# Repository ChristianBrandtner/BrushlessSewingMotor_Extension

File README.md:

# BrushlessSewingMotor_Extension
&nbsp;&nbsp;&nbsp;&nbsp;&nbsp;&nbsp;&nbsp;&nbsp;&nbsp;&nbsp;

contact: github1@brandtner.net

## 11/2022  ! Project is in progress, ask before you order PCB or other things. !

## INTRODUCTION

This is a extension for a cheap chinese 550/750W brushless servo motor for external control of speed, direction, etc.
to use in in e.g. Mini Lathe

first test with switch and potentiometer:
https://www.youtube.com/watch?v=qao7Rex1lZU

## STATUS
7.11.2024

Ein neues ISO Interface ist in Arbeit aber noch nicht fertiggestellt. 
Die Software ermöglicht es jetzt die komplette Steuerung des Motorkontollers zu übernehmen, inklusive der Einstellungen für die Motorparameter im Kontroller. Das bedeutet daß das Bedienpanel des BLDC-Motors nicht mehr in Griffweite sein muss.

Im Moment pausiert die Entwicklung weil zuwenig Bedarf dafür zu erkennen ist.

A new ISO interface is in the works but not yet finished. The software now makes it possible to take over complete control of the motor controller, including the settings for the motor parameters in the controller. This means that the control panel of the BLDC motor no longer has to be within reach.

Development is currently on hold because there is not enough demand for it.

14.2.2023

RPM Sensor

05.09.2022

Beim Einbau in das Steuergehäuse habe ich nun festgestellt das es Änderungsbedarf gibt, es ist ziemlich eng und die Anordnung der Anschlüsse passt nicht so wirklich gut.

Deshalb wird es eine zweigeteilte Lösung geben, 1. das Iso Ínterface, montiert auf dem SMC Controller, 2. davon getrennt die Steuerungsplatine, dann neu mit einem Ardunino Nano wegen der USB-Schnittstelle für einfache Updates.
Durch die Trennung ergibt sich auch die Mögichkeit eine andere Steuerung zu verwenden, z.B. Blackpill STM32F411. Der Ardunio ist schon arg an der Grenze des Flashspeichers.

Next Version (11/2022):

08.07.2022

Die ursprüngĺiche Planung auf eine Hardwaredrehzahlmessung zu verzichten werde ich nicht mehr weiterverfolgen.
Die Softwarelösung funktioniert zwar zufriedenstellend, auch unter berücksichtigung des Getriebeschalters und der Untersetzungen von Motor und Getriebe, aber der Atmega ist durch die vielen Einstellungsmenüs am Ende der Kapazität.
Deshalb ist ein Drehzahlsensor an der Spindel erforderlich, damit entfällt die ganze Software für die Drehzahlberechnung und es ist Platz um die Schnittgeschwindigkeit für den Werkstückdurchmesser anzuzeigen.
Das finde ich nützlicher als den Drehzahlsensor einzusparen.
An der Hardware der Platine ändert sich nichts, war alles schon vorgesehen.

07.07.2022

Version 14.5

Änderungen an der Platine
Grund:
Einfügen eines optionalen ISP-Steckers.
Anschluss der RPM Sensors nach PB0 (ICP1) verlegt.
optinonal weitere Anschlussbuchse für den Pedalanschluss vorgesehen, zum direkten Kabelanschluss des Pedalkabels
an den originalen Stecker des SMC. Kein zusätzlicher JST Stecker J9 auf dem SMC Board notwendig. 

22.6.2022

Version 14.2

Änderungen an der Platine
Grund:
JST Stecker J3 Fehler in der Ausrichtung beseitigt

20.6.2022

Version 14.1

Änderungen an der Platine
Grund:
OK2 Anschlüsse vertauscht, optionale Widerstände R6,R30,R31
JST Stecker J3, Ausrichtung getauscht damit fertig konfektionierte Kabel zum SMC verwendet werden können.
Schaltung getestet (ohne RPM-Sensor und analog 0-10V Eingang, alles optional)

Wesentliche Funktionen der Software funktionieren:
Drehzahlregelung, Richtungsumschaltung, Drehzahlanzeige

03.06.2022 New PCB Version 12.2, Errors in PCB layout fixed. Basic software in progress.

12.05.2022 PCB Version 11.5 with galvanic isolation is in production 

30.04.2022 The goal is to fit the SMC controller board and everything else into the existing lathe front casing.

29.04.2022 optoisolation with separate powersupply is in work.

28.04.2022 under construction and brainstorming.

## PREVIEW

## TODO

TODO: finalize software

## Features

- no changes on Controlerboard or Panelboard needed; 
- can be installed in the housing on existing attachments; 
- speedcontrol, rotary encoder;
- start/stop control,  button with LED; 
- rotation direction control, button with LED;
- securityswitch input for chuck guard;
- spindel RPM display (calculated and maesured)
- original SMC displaypanel can be used at same time 
- high temperture warning;
- rampup and down at start/stop
- isolated inputs/outputs for galvanic isolation from the mains voltage

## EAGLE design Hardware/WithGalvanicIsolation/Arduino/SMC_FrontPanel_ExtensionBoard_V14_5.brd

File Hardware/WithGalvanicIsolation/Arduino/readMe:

this version will no longer be pursued.
14.2.2023

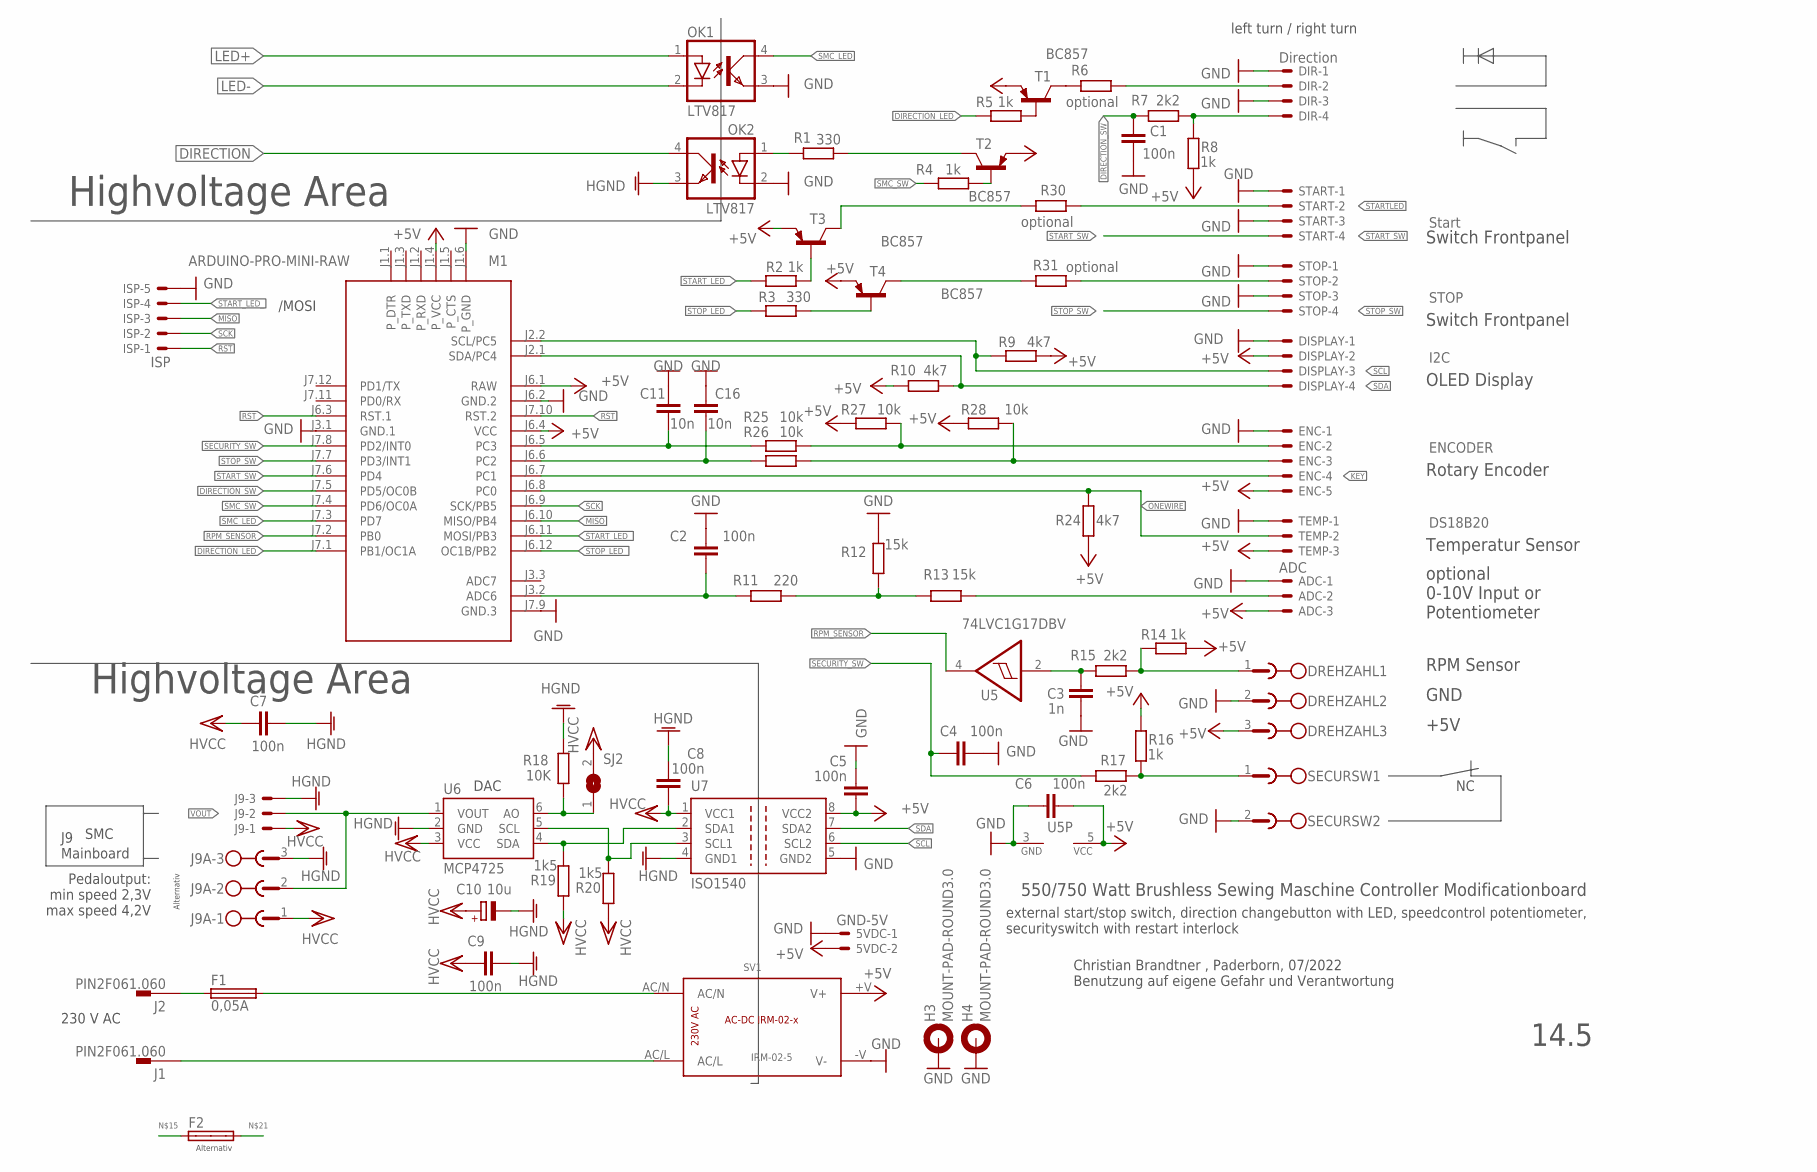
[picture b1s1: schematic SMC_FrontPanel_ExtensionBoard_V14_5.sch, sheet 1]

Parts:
5VDC: GND-5V; JST-XH-02-PACKAGE-ROUND-PAD
ADC: ADC; JST-XH-03-PACKAGE-ROUND-PAD
C1, C2, C4, C5, C6, C7, C8, C9: 100n; C0805
C3: 1n; C0805
C10: 10u; 153CLV-0405
C11, C16: 10n; C0805
DIR: Direction; JST-XH-04-PACKAGE-ROUND-PAD
DISPLAY: I2C; JST-XH-04-PACKAGE-ROUND-PAD
DREHZAHL: MCV_1.5/3/-G-3.5; 1843619
ENC: ENCODER; JST-XH-05-PACKAGE-ROUND-PAD
F1: 0,05A; MTA501100
F2: SHK20L
H3, H4: MOUNT-PAD-ROUND3.0; 3,0-PAD
ISP: ISP; JST-XH-05-PACKAGE-ROUND-PAD
J1, J2: PIN2F061.060; F061.060
J9: JST-XH-03-PIN-ROUND-PAD; JST-XH-03-PACKAGE-ROUND-PAD
J9A-: MCV_1.5/3/-G-3.5; 1843619
M1: ARDUINO-PRO-MINI-RAW; ARDUINO-PRO-MINI
OK1, OK2: LTV817; SMD4-7
R1, R3: 330; R0805
R2, R4, R5, R8, R14, R16: 1k; R0805
R6, R30, R31: optional; R0805
R7, R15, R17: 2k2; R0805
R9, R10, R24: 4k7; R0805
R11: 220; R0805
R12, R13: 15k; R0805
R18: 10K; R0805
R19, R20: 1k5; R0805
R25, R26, R27, R28: 10k; R0805
SECURSW: MCV_1,5/2-G-3,5; 1843606
SJ2: SJ
START: Start; JST-XH-04-PACKAGE-ROUND-PAD
STOP: STOP; JST-XH-04-PACKAGE-ROUND-PAD
SV1: IRM-02-5; IRM-02-X
T1, T2, T3, T4: BC857; SOT23-BEC
TEMP: DS18B20; JST-XH-03-PACKAGE-ROUND-PAD
U5: 74LVC1G17DBV; SOT23-5
U6: MCP4725; SOT23-6
U7: ISO1540; SO-08

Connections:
+5V: 5VDC.2, ADC.3, C5.1, C6.1, DISPLAY.2, DREHZAHL.3, ENC.5, M1.J1.4 (P_VCC), M1.J6.1 (RAW), M1.J6.4 (VCC), R8.2, R9.1, R10.1, R14.1, R16.1, R24.2, R27.1, R28.1, SV1.+V (V+), T1.E, T2.E, T3.E, T4.E, TEMP.3, U5.5 (VCC), U7.8 (VCC2)
ADC_POTI: C2.1, M1.J3.2 (ADC6), R11.1
DIRECTION: OK2.4 (COL); also elsewhere on the board
DIRECTION_LED: M1.J7.1 (PB1/OC1A), R5.2
DIRECTION_SW: C1.2, M1.J7.5 (PD5/OC0B), R7.1
GND: 5VDC.1, ADC.1, C1.1, C2.2, C3.1, C4.2, C5.2, C6.2, C11.2, C16.2, DIR.1, DIR.3, DISPLAY.1, DREHZAHL.2, ENC.1, H3.B3,0, H4.B3,0, ISP.5, M1.J1.6 (P_GND), M1.J3.1 (GND.1), M1.J6.2 (GND.2), M1.J7.9 (GND.3), OK1.3 (EMIT), OK2.2 (C), R12.2, SECURSW.2, START.1, START.3, STOP.1, STOP.3, SV1.-V (V-), TEMP.1, U5.3 (GND), U7.5 (GND2)
HGND: C7.1, C8.2, C9.1, C10.-, J9.3, J9A-.3, OK2.3 (EMIT), R18.1, U6.2 (GND), U7.4 (GND1); also elsewhere on the board
HVCC: C7.2, C8.1, C9.2, C10.+, J9.1, J9A-.1, R19.2, R20.2, SJ2.2, U6.3 (VCC), U7.1 (VCC1); also elsewhere on the board
KEY: ENC.4, M1.J6.7 (PC1)
LED+: OK1.1 (A); also elsewhere on the board
LED-: OK1.2 (C); also elsewhere on the board
MISO: ISP.3, M1.J6.10 (MISO/PB4)
unnamed: OK2.1 (A), R1.2
unnamed: R1.1, T2.C
unnamed: R30.1, START.2
unnamed: R2.1, T3.B
unnamed: C3.2, R15.1, U5.2 (I)
unnamed: R3.1, T4.B
unnamed: R18.2, SJ2.1, U6.6 (AO)
unnamed: F1.1, F2.1A, J2.A1, J2.A2
unnamed: DREHZAHL.1, R14.2, R15.2
unnamed: R16.2, R17.2, SECURSW.1
unnamed: R31.2, T4.C
unnamed: R11.2, R12.1, R13.2
unnamed: ADC.2, R13.1
unnamed: F1.2, F2.2A, SV1.AC/N
unnamed: J1.A1, J1.A2, SV1.AC/L
unnamed: R6.2, T1.C
unnamed: DIR.2, R6.1
unnamed: R5.1, T1.B
unnamed: R4.1, T2.B
unnamed: R20.1, U6.5 (SCL), U7.3 (SCL1)
unnamed: DIR.4, R7.2, R8.1
unnamed: C16.1, M1.J6.6 (PC2), R26.1
unnamed: C11.1, M1.J6.5 (PC3), R25.1
unnamed: ENC.2, R25.2, R27.2
unnamed: ENC.3, R26.2, R28.2
unnamed: R31.1, STOP.2
ONEWIRE: M1.J6.8 (PC0), R24.1, TEMP.2
RPM_SENSOR: M1.J7.2 (PB0), U5.4 (O)
RST: ISP.1, M1.J6.3 (RST.1), M1.J7.10 (RST.2)
SCK: ISP.2, M1.J6.9 (SCK/PB5)
SCL: DISPLAY.3, M1.J2.2 (SCL/PC5), R9.2, U7.6 (SCL2)
SDA: DISPLAY.4, M1.J2.1 (SDA/PC4), R10.2, U7.7 (SDA2)
SDA_HV: R19.1, U6.4 (SDA), U7.2 (SDA1)
SECURITY_SW: C4.1, M1.J7.8 (PD2/INT0), R17.1
SMC_LED: M1.J7.3 (PD7), OK1.4 (COL)
SMC_SW: M1.J7.4 (PD6/OC0A), R4.2
STARTLED: R30.2, T3.C
START_LED_: ISP.4, M1.J6.11 (MOSI/PB3), R2.2
START_SW: M1.J7.6 (PD4), START.4
STOP_LED_: M1.J6.12 (OC1B/PB2), R3.2
STOP_SW: M1.J7.7 (PD3/INT1), STOP.4
VOUT: J9.2, J9A-.2, U6.1 (VOUT)

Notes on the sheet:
left turn / right turn
SMC
Pedaloutput: min speed 2,3V max speed 4,2V
DAC
Highvoltage Area
14.5
OLED Display
Rotary Encoder
Temperatur Sensor
Switch Frontpanel
optional 0-10V Input or Potentiometer
RPM Sensor
550/750 Watt Brushless Sewing Maschine Controller Modificationboard
external start/stop switch, direction changebutton with LED, speedcontrol potentiometer, securityswitch with restart interlock
Christian Brandtner , Paderborn, 07/2022 Benutzung auf eigene Gefahr und Verantwortung
230 V AC
J9 Mainboard
+5V
GND
Alternativ
/MOSI

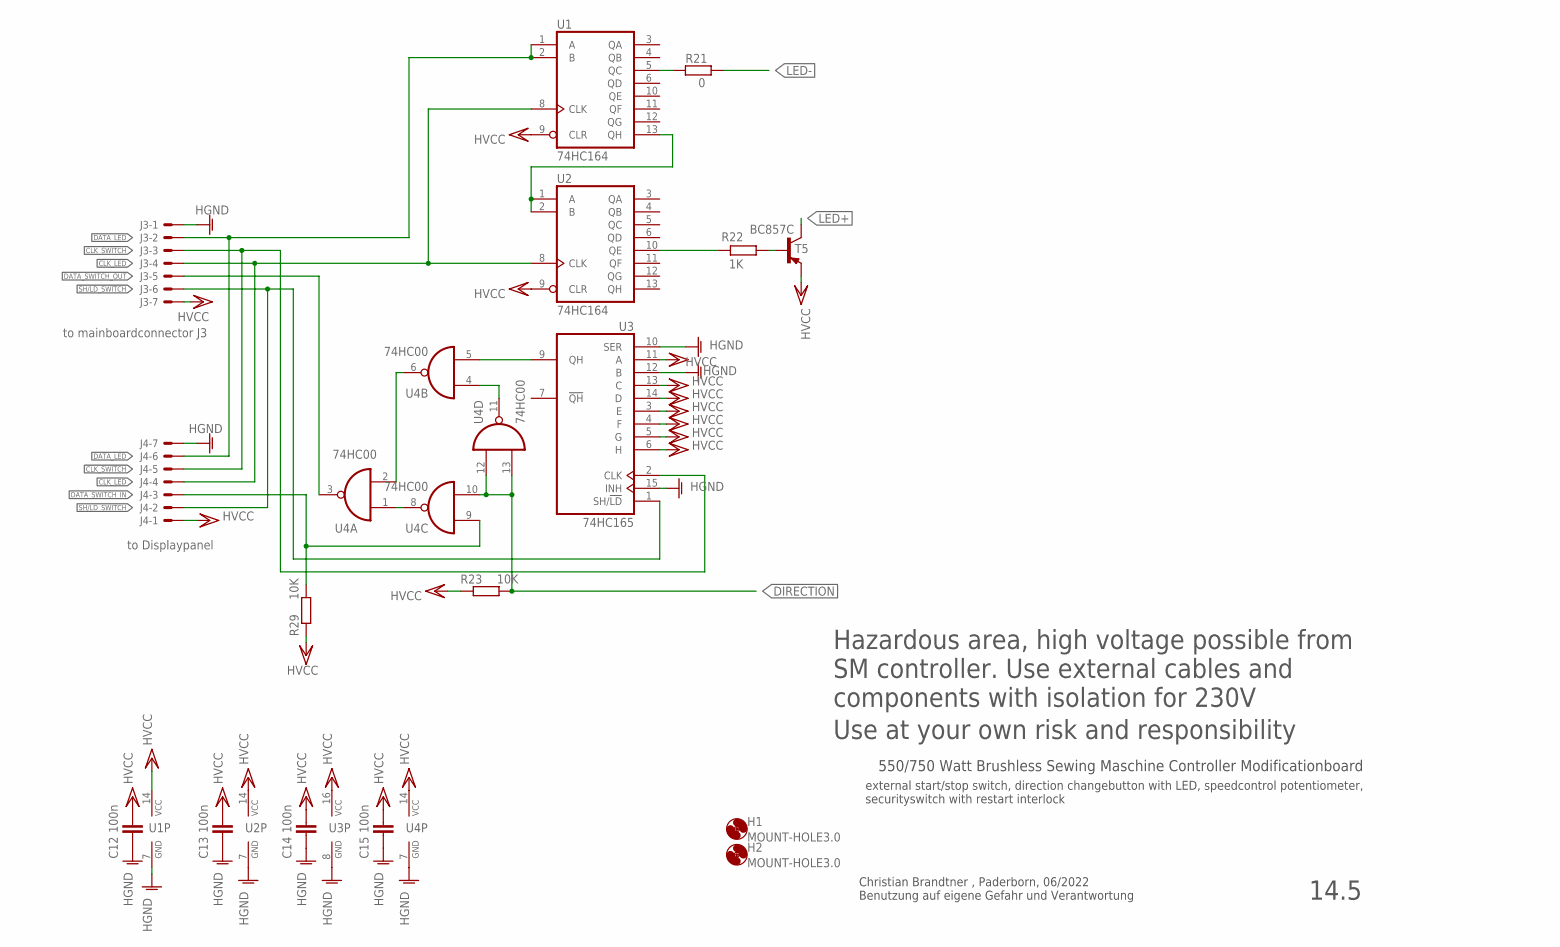
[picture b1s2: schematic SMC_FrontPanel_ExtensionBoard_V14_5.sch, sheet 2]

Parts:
C12, C13, C14, C15: 100n; C0805
H1, H2: MOUNT-HOLE3.0; 3,0
J3: to mainboardconnector J3; JST-XH-07-PACKAGE-ROUND-PAD
J4: to Displaypanel; JST-XH-07-PACKAGE-ROUND-PAD
R21: 0; R0805
R22: 1K; R0805
R23, R29: 10K; R0805
T5: BC857C; SOT23-BEC
U1, U2: 74HC164; SO14
U3: 74HC165; SO16
U4: 74HC00; SO14

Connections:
CLK_LED: J3.4, J4.4, U1.8 (CLK), U2.8 (CLK)
CLK_SWITCH: J3.3, J4.5, U3.2 (CLK)
DATA_LED: J3.2, J4.6, U1.1 (A), U1.2 (B)
DATA_SWITCH_IN: J4.3, R29.1, U4.9 (I0)
DATA_SWITCH_OUT: J3.5, U4.3 (O)
DIRECTION: R23.1, U4.10 (I1), U4.12 (I0), U4.13 (I1); also elsewhere on the board
G: U1.13 (QH), U2.1 (A), U2.2 (B)
HGND: C12.1, C13.1, C14.1, C15.1, J3.1, J4.7, U1.7 (GND), U2.7 (GND), U3.8 (GND), U3.10 (SER), U3.12 (B), U3.15 (INH), U4.7 (GND); also elsewhere on the board
HVCC: C12.2, C13.2, C14.2, C15.2, J3.7, J4.1, R23.2, R29.2, T5.E, U1.9 (CLR), U1.14 (VCC), U2.9 (CLR), U2.14 (VCC), U3.3 (E), U3.4 (F), U3.5 (G), U3.6 (H), U3.11 (A), U3.13 (C), U3.14 (D), U3.16 (VCC), U4.14 (VCC); also elsewhere on the board
LED+: T5.C; also elsewhere on the board
LED-: R21.2; also elsewhere on the board
unnamed: R22.1, T5.B
unnamed: R21.1, U1.5 (QC)
unnamed: U3.9 (QH), U4.5 (I1)
unnamed: U4.2 (I1), U4.6 (O)
unnamed: U4.1 (I0), U4.8 (O)
unnamed: U4.4 (I0), U4.11 (O)
unnamed: R22.2, U2.10 (QE)
SH/LD_SWITCH: J3.6, J4.2, U3.1 (SH/!LD)

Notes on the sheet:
550/750 Watt Brushless Sewing Maschine Controller Modificationboard
external start/stop switch, direction changebutton with LED, speedcontrol potentiometer, securityswitch with restart interlock
Hazardous area, high voltage possible from SM controller. Use external cables and components with isolation for 230V
Christian Brandtner , Paderborn, 06/2022 Benutzung auf eigene Gefahr und Verantwortung
14.5
Use at your own risk and responsibility

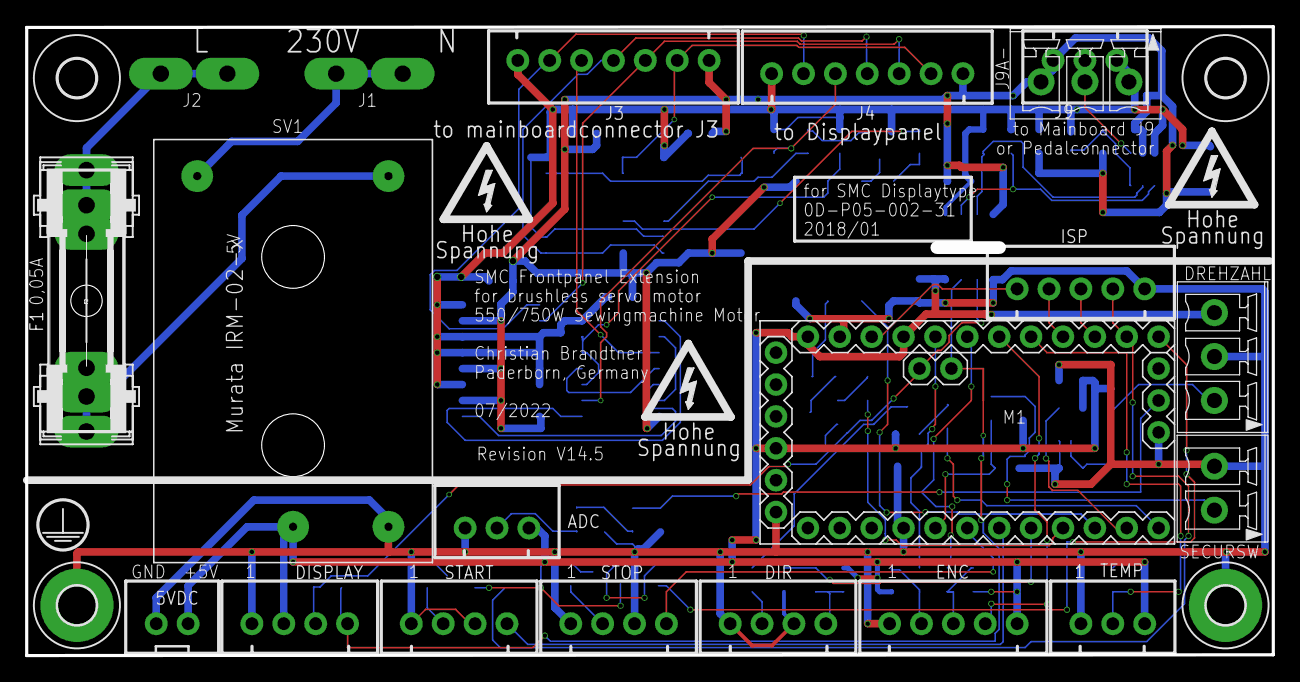
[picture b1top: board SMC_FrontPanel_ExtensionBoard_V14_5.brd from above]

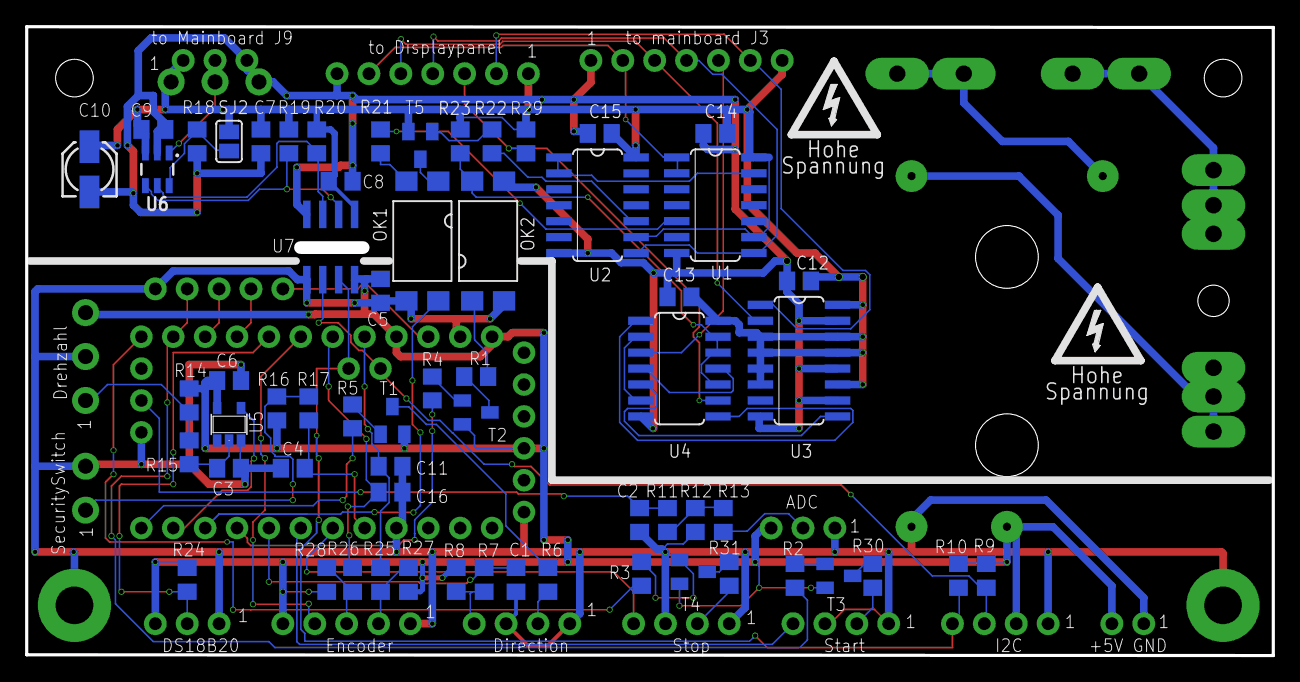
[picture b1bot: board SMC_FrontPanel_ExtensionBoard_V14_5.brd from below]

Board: 2 copper layers, 98.5 x 49.3 mm, 93 parts (62 on the bottom side), 68 nets.

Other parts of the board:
U$53, U$54, U$57: HIGHVOLT1_TOP
U$55, U$56: HIGHVOLT1_BOT
U$58: SCHUTZLEITER

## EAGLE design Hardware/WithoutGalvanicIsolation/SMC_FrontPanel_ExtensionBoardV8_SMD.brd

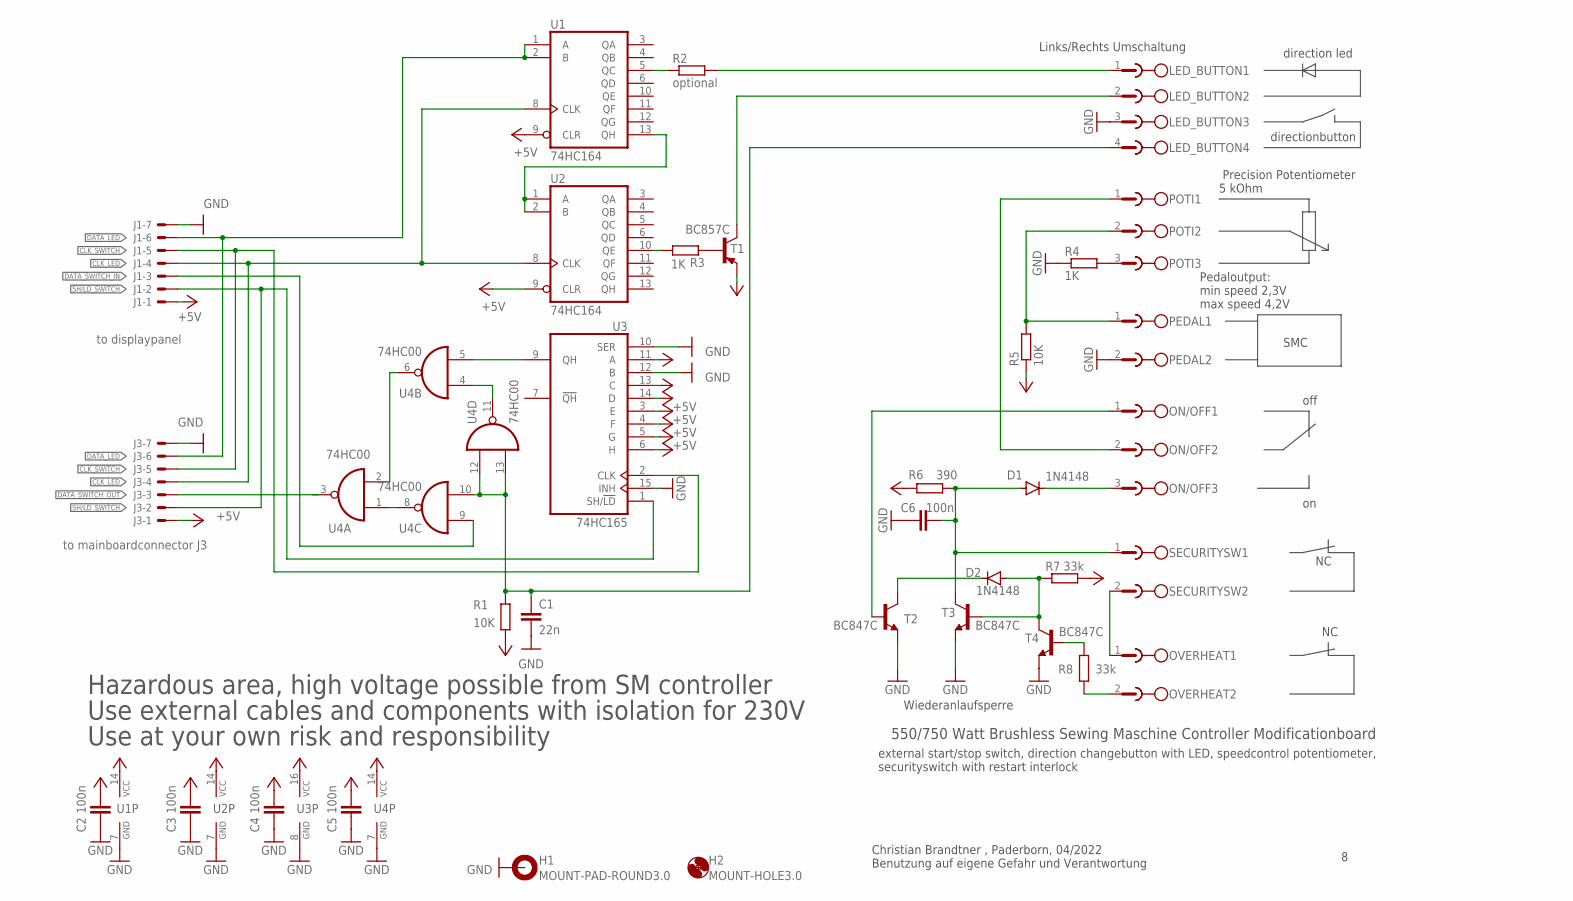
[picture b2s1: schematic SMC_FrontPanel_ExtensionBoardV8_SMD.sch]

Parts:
C1: 22n; C0805
C2, C3, C4, C5, C6: 100n; C0805
D1, D2: 1N4148; SOD323-W
H1: MOUNT-PAD-ROUND3.0; 3,0-PAD
H2: MOUNT-HOLE3.0; 3,0
J1: to displaypanel; JST-XH-07-PACKAGE-ROUND-PAD
J3: to mainboardconnector J3; JST-XH-07-PACKAGE-ROUND-PAD
LED_BUTTON: MC_1.5/4_G_3.5; MC_1.5/4-G-3.5
ON/OFF: MC_1.5/3-G-3.5
OVERHEAT: MC_1.5/2-G-3.5
PEDAL: MC_1.5/2-G-3.5
POTI: MC_1.5/3-G-3.5
R1, R5: 10K; R0805
R2: optional; R0805
R3, R4: 1K; R0805
R6: 390; R0805
R7, R8: 33k; R0805
SECURITYSW: MC_1.5/2-G-3.5
T1: BC857C; SOT23-BEC
T2, T3, T4: BC847C; SOT23-BEC
U1, U2: 74HC164; SO14
U3: 74HC165; SO16
U4: 74HC00; SO14

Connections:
+5V: C2.2, C3.2, C4.2, C5.2, J1.1, J3.1, R1.2, R5.1, R6.2, R7.1, T1.E, U1.9 (CLR), U1.14 (VCC), U2.9 (CLR), U2.14 (VCC), U3.3 (E), U3.4 (F), U3.5 (G), U3.6 (H), U3.11 (A), U3.13 (C), U3.14 (D), U3.16 (VCC), U4.14 (VCC)
CLK_LED: J1.4, J3.4, U1.8 (CLK), U2.8 (CLK)
CLK_SWITCH: J1.5, J3.5, U3.2 (CLK)
DATA_LED: J1.6, J3.6, U1.1 (A), U1.2 (B)
DATA_SWITCH_IN: J1.3, U4.9 (I0)
DATA_SWITCH_OUT: J3.3, U4.3 (O)
G: U1.13 (QH), U2.1 (A), U2.2 (B)
GND: C1.2, C2.1, C3.1, C4.1, C5.1, C6.1, H1.B3,0, J1.7, J3.7, LED_BUTTON.3, PEDAL.2, R4.1, T2.E, T3.E, T4.E, U1.7 (GND), U2.7 (GND), U3.8 (GND), U3.10 (SER), U3.12 (B), U3.15 (INH), U4.7 (GND)
unnamed: R3.1, T1.B
unnamed: LED_BUTTON.1, R2.2
unnamed: R2.1, U1.5 (QC)
unnamed: LED_BUTTON.2, T1.C
unnamed: ON/OFF.2, POTI.1
unnamed: POTI.3, R4.2
unnamed: PEDAL.1, POTI.2, R5.2
unnamed: R8.1, T4.B
unnamed: U3.9 (QH), U4.5 (I1)
unnamed: U4.2 (I1), U4.6 (O)
unnamed: OVERHEAT.2, R8.2
unnamed: U4.1 (I0), U4.8 (O)
unnamed: U4.4 (I0), U4.11 (O)
unnamed: C1.1, LED_BUTTON.4, R1.1, U4.10 (I1), U4.12 (I0), U4.13 (I1)
unnamed: ON/OFF.1, T2.B
unnamed: D1.C, ON/OFF.3
unnamed: C6.2, D1.A, R6.1, SECURITYSW.1, T3.C
unnamed: D2.C, T2.C
unnamed: OVERHEAT.1, SECURITYSW.2
unnamed: D2.A, R7.2, T3.B, T4.C
unnamed: R3.2, U2.10 (QE)
SH/LD_SWITCH: J1.2, J3.2, U3.1 (SH/!LD)

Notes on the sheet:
Links/Rechts Umschaltung
direction led
directionbutton
off
Wiederanlaufsperre
SMC
550/750 Watt Brushless Sewing Maschine Controller Modificationboard
external start/stop switch, direction changebutton with LED, speedcontrol potentiometer, securityswitch with restart interlock
Precision Potentiometer 5 kOhm
Hazardous area, high voltage possible from SM controller
Use external cables and components with isolation for 230V
Christian Brandtner , Paderborn, 04/2022 Benutzung auf eigene Gefahr und Verantwortung
Use at your own risk and responsibility
Pedaloutput: min speed 2,3V max speed 4,2V

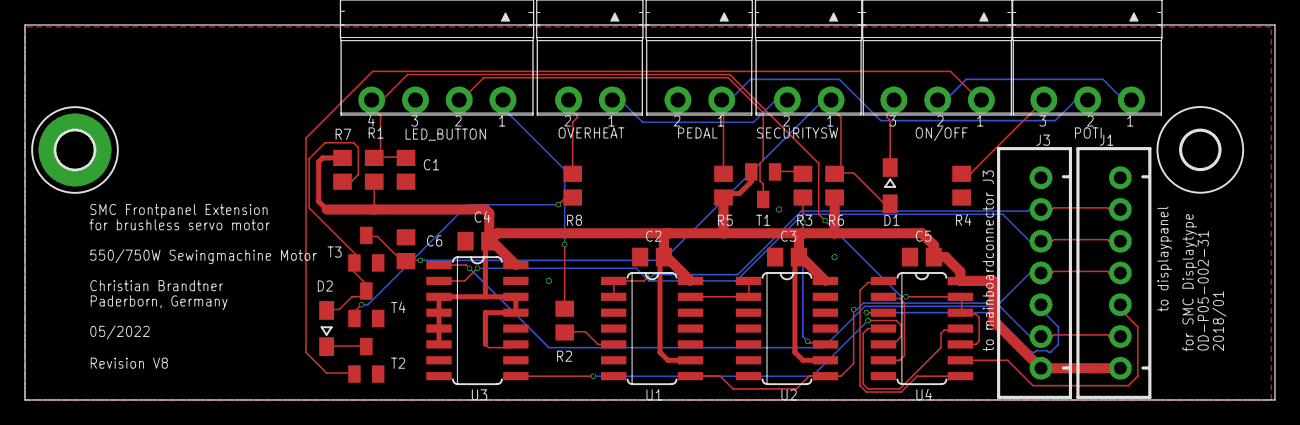
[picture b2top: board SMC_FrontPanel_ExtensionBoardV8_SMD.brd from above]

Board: 2 copper layers, 100.0 x 30.0 mm, 34 parts (0 on the bottom side), 30 nets.

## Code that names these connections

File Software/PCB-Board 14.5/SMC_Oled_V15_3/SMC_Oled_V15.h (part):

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#define ENCODER_BTN	  A1
#define ENCODER_STEPS_PER_NOTCH    4   // Change this depending on which encoder is used

#define START_BUTTON_PIN 	PD4
#define START_LED_PIN		11
#define STOP_BUTTON_PIN 	PD3
#define STOP_LED_PIN		10
#define DIR_BUTTON_PIN 		PD5

#define DIR_LED_PIN			9
#define BOARD_LED_PIN		13

#define RPM_SENSOR_PIN		8
#define SECURITY_SW_PIN		PD2
#define	SMC_DP4_PIN			PD7			// Input from SMC
#define SMC_SW_PIN			PD6			// Output to SMC
#define	ADC_INPUT_PIN		A6

#define START_LED		0
#define STOP_LED		1
#define DIR_LED			2
#define BOARD_LED		3

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
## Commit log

2022-05-04 reorg
2022-05-04 Update Doc
2022-05-04 Update Frontpanel_V4
2022-05-04 Update Step2
2022-05-05 Update Schematic
2022-05-06 Update Board , Schematic
2022-05-09 Frontplatte
2022-05-11 diverse Änderungen
2022-05-12 Version 10.5 in production JLCPCB
2022-05-31 Diverse Fehler beseitigt, siehe Readme
2022-05-31 Create License
2022-06-02 Update issue templates
2022-06-03 Fehlerbeseitigung siehe Readme
2022-06-05 Delete SMC_FrontPanel_ExtensionBoard_Step2_V12_2.brd
    Gravierender Fehler im Layout
2022-06-05 Delete SMC_FrontPanel_ExtensionBoard_Step2_V12_2.sch
    Gravierender Fehler im Layout
2022-06-05 Delete SMC_FrontPanel_ExtensionBoard_Step2_V12_2.pdf
    Gravierender Fehler im Layout
2022-06-05 Delete SMC_FrontPanel_ExtensionBoard_Step2_V11_5_TOP.pdf
    Gravierender Fehler im Layout
2022-06-05 Delete SMC_FrontPanel_ExtensionBoard_Step2_V11_5_BOT.pdf
    Gravierender Fehler im Layout
2022-06-05 Delete SMC_FrontPanel_ExtensionBoard_Step2_V11_5_SCH.pdf
    Gravierender Fehler im Layout
2022-06-21 Diverse Änderungen an der Platine
2022-06-21 Display
2022-06-22 Update Revision 14.2 J3 Ausrichtung getauscht um fertige Kabel verwenden zu können. Kosmetik
2022-06-22 remove old version
2022-07-07 Änderungen an der Platine
2022-07-08 Update Softwareplanung
2022-07-26 Bilder vom Motoreinbau in EDM300
2022-07-26 Bilder geändert
2022-09-05 geplante Änderungen
2022-11-09 diverse updates, pictures etc.
2022-11-11 Directory and new Hardwareversion
2022-11-11 New ISO-Interface
2022-11-11 first view
2022-11-15 updates und Test
2022-11-16 wrong files corrected
2022-12-01 !!Servere Error in the footprint of the Arduino Micro!!, do not connect the left connector (with RxD,TxD,DTR, etc.) to the board.
2023-02-14 PCB Board 14.5 Hard and Software
2023-03-21 Update README.md
    Planend new Features
2023-03-22 Firstview of ISO Interface 4.4 with Mach3 Option or external potentiometer for speedcontrol and switch for direction change
2023-03-22 smaller picture
2023-06-16 Hexfile to flash
2023-09-09 Basic documents addition
2023-09-26 Files waren unvollständig
2023-09-26 diverse Updates und Ergänzungen
2023-09-26 Adding Gerberfiles
2024-01-24 Test and EEPROM Configuration
2024-01-24 Do not equip R27,R28 if the encoder used has a circuit board with resistors
2024-03-13 some minor changes

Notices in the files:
Software/PCB-Board 14.5/SMC_Oled_V15_3/SMC_Oled_V15.h:
define _RIGHTS_ "GPL-3.0 license"
README.md:
License: GPL v3
parts and their libraries:
SparkFun-IC-Conversion: Licensing: Creative Commons ShareAlike 4.0 International - https://creativecommons.org/licenses/by-sa/4.0
diy-modules: Released under the Creative Commons Attribution 4.0 International License: http://creativecommons.org/licenses/by/4.0
